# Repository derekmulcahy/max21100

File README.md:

max21100
========

Breakout board for MAX21100 Low-Power, Ultra-Accurate 6+3 DoF IMU

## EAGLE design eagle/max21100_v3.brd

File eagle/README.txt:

max21100_v1 - Initial version, tested and working.
max21100_v2 - untested
    Add I2C jumper (tying CS high) to select I2C mode.
    Add SAO jumper to select address for I2C.
    V2 label
    Increase label sizes and reposition
    Move dsync, int1 and int2 headers pins to simplify board.
    Rename labels to reflect default I2C usage, SCK->SCL, SDO->SA0, SDI->CS
    Remove central via and label under chip.
    Improve via positions and straighten traces from chip.
max21100_v3 - untested
    Shortened pin labels.
    Moved MDA, MCL, SCL, SDA, CS and SA0 headers to simplify layout.
    Moved jumpers and removed default for I2C and SA0 jumpers.
    Renumbered capactitors.
    Swapped positions of R1 and R2.
    Added pin 1 marker.

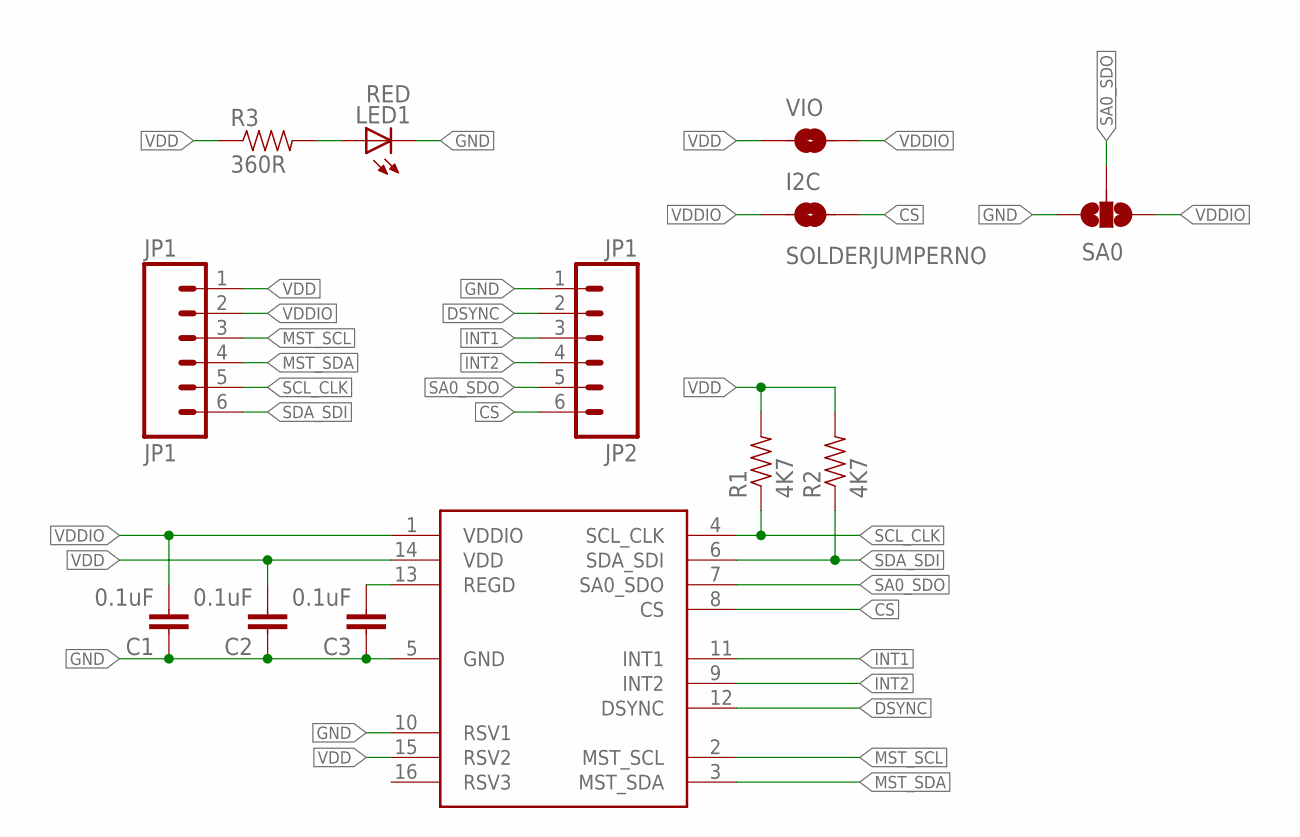
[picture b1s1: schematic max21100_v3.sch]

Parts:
C1, C2, C3: 0.1uF; 0603-CAP
I2C: SOLDERJUMPERNO; SJ_2S-NO
JP1, JP2: JP1; 1X06
LED1: RED; CHIP-LED0603
R1, R2: 4K7; 0603-RES
R3: 360R; 0603-RES
SA0: SOLDERJUMPER_2WAYS; SJ_3
U$1: MAX21100
VIO: SOLDERJUMPERTRACE; SJ_2S-TRACE

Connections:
CS: I2C.2, JP2.6, U$1.8 (CS)
DSYNC: JP2.2, U$1.12 (DSYNC)
GND: C1.1, C2.1, C3.1, JP2.1, LED1.C, SA0.1, U$1.5 (GND), U$1.10 (RSV1)
INT1: JP2.3, U$1.11 (INT1)
INT2: JP2.4, U$1.9 (INT2)
MST_SCL: JP1.3, U$1.2 (MST_SCL)
MST_SDA: JP1.4, U$1.3 (MST_SDA)
unnamed: LED1.A, R3.2
REGD: C3.2, U$1.13 (REGD)
SA0_SDO: JP2.5, SA0.2, U$1.7 (SA0_SDO)
SCL_CLK: JP1.5, R1.1, U$1.4 (SCL_CLK)
SDA_SDI: JP1.6, R2.1, U$1.6 (SDA_SDI)
VDD: C2.2, JP1.1, R1.2, R2.2, R3.1, U$1.14 (VDD), U$1.15 (RSV2), VIO.1
VDDIO: C1.2, I2C.1, JP1.2, SA0.3, U$1.1 (VDDIO), VIO.2

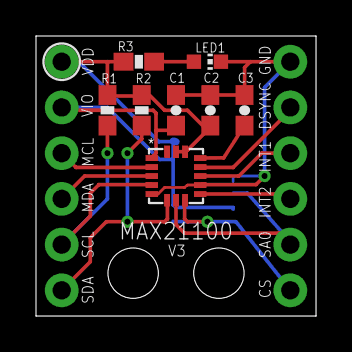
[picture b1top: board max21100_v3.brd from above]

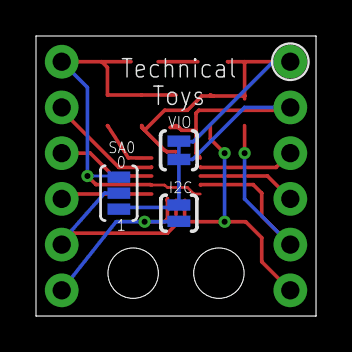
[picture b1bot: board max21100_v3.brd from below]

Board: 2 copper layers, 15.6 x 15.6 mm, 13 parts (3 on the bottom side), 14 nets.

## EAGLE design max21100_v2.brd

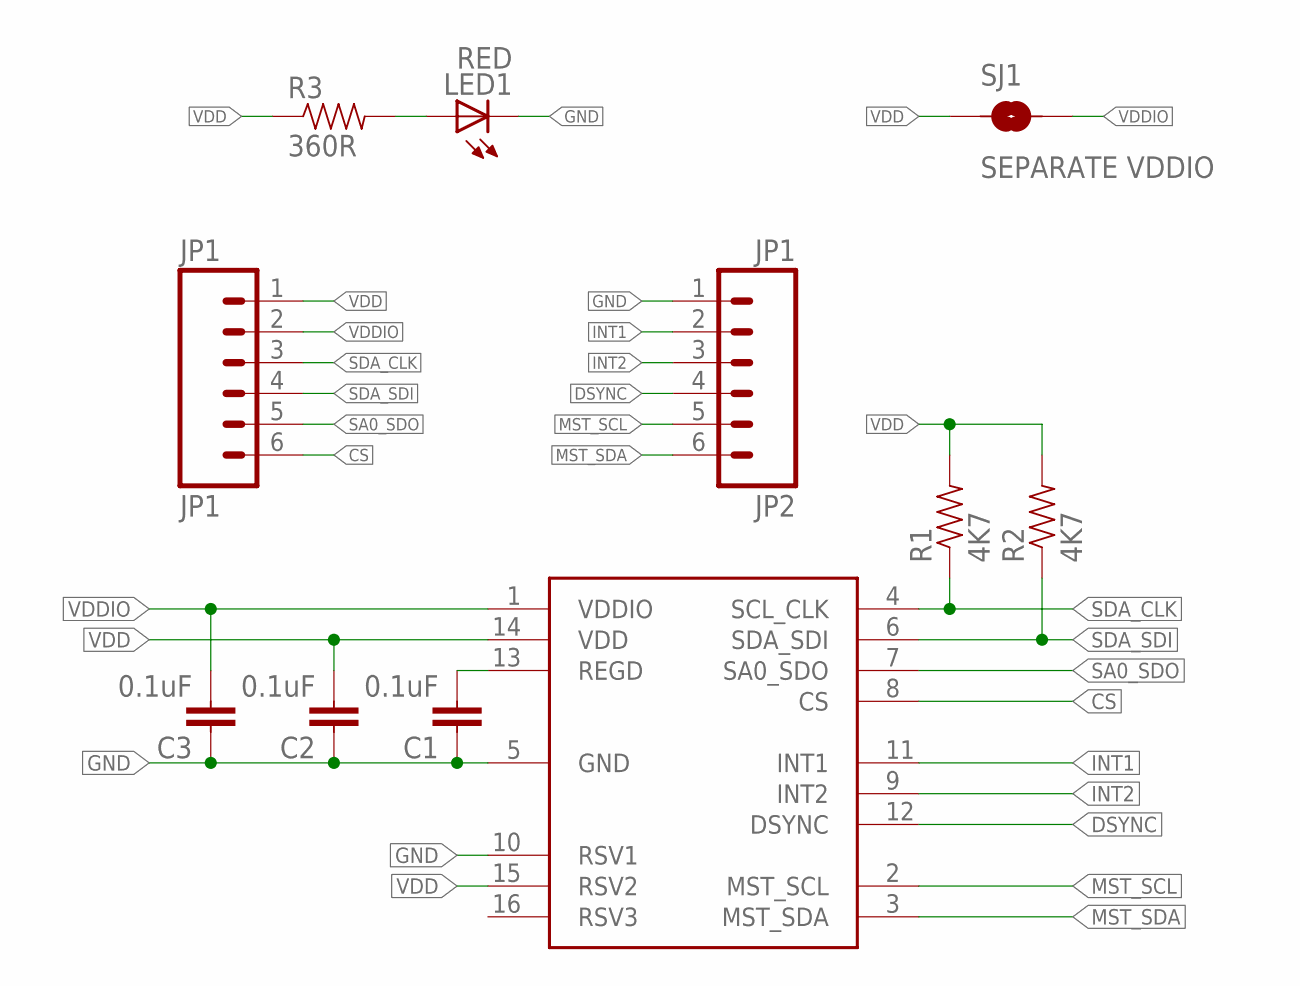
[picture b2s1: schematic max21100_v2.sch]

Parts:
C1, C2, C3: 0.1uF; 0603-CAP
JP1, JP2: JP1; 1X06
LED1: RED; CHIP-LED0603
R1, R2: 4K7; 0603-RES
R3: 360R; 0603-RES
SJ1: SEPARATE VDDIO; SJ_2S-TRACE
U$1: MAX21100

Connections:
CS: JP1.6, U$1.8 (CS)
DSYNC: JP2.4, U$1.12 (DSYNC)
GND: C1.1, C2.1, C3.1, JP2.1, LED1.C, U$1.5 (GND), U$1.10 (RSV1)
INT1: JP2.2, U$1.11 (INT1)
INT2: JP2.3, U$1.9 (INT2)
MST_SCL: JP2.5, U$1.2 (MST_SCL)
MST_SDA: JP2.6, U$1.3 (MST_SDA)
unnamed: LED1.A, R3.2
REGD: C1.2, U$1.13 (REGD)
SA0_SDO: JP1.5, U$1.7 (SA0_SDO)
SDA_CLK: JP1.3, R1.1, U$1.4 (SCL_CLK)
SDA_SDI: JP1.4, R2.1, U$1.6 (SDA_SDI)
VDD: C2.2, JP1.1, R1.2, R2.2, R3.1, SJ1.1, U$1.14 (VDD), U$1.15 (RSV2)
VDDIO: C3.2, JP1.2, SJ1.2, U$1.1 (VDDIO)

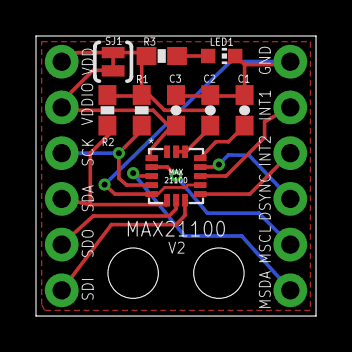
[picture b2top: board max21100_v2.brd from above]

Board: 2 copper layers, 15.6 x 15.6 mm, 12 parts (1 on the bottom side), 14 nets.

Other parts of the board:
U$2: OSHW_8X200_NOTEXT

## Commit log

2014-02-02 Initial commit of eagle files
2014-02-02 Created eagle directory
2014-02-09 Improved V2

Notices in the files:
parts and their libraries:
SparkFun-Passives: Licensing: CC v3.0 Share-Alike You are welcome to use this library for commercial purposes.
